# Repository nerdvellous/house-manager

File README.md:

house-manager
=============

Repository du projet "HouseManager"

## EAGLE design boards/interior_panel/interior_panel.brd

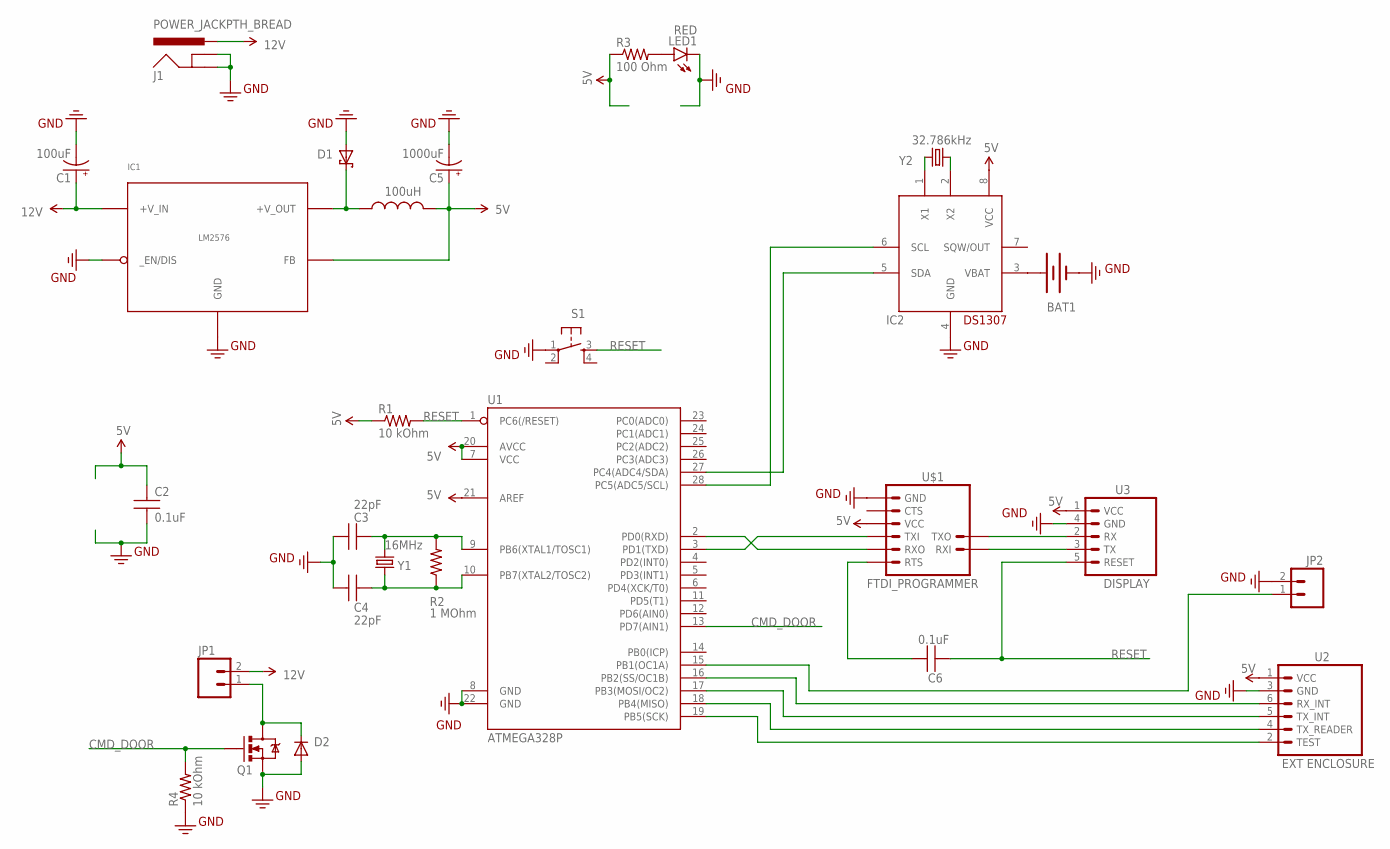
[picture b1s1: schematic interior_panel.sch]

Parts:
BAT1: BATTERY12MMFULLPTH; BATTCON_12MM_FULLPTH
C1: 100uF; CPOL-RADIAL-100UF-25V
C2, C6: 0.1uF; CAP-PTH-SMALL
C3, C4: 22pF; CAP-PTH-SMALL
C5: 1000uF; CPOL-RADIAL-100UF-25V
D1: 1N5822; DO-201AD
D2: 1N4004; DO-41
IC1: LM2576; TO-220-5PIN
IC2: DS1307; DIL08
J1: POWER_JACKPTH_BREAD; POWER_JACK_PTH_BREAD
JP1, JP2: M02PTH; 1X02
L1: 100uH; RLB0912
LED1: RED; LED5MM
Q1: MOSFET-NCHANNELFQP30N06L; TO220V
R1, R4: 10 kOhm; AXIAL-0.3
R2: 1 MOhm; AXIAL-0.3
R3: 100 Ohm; AXIAL-0.3
S1: TAC_SWITCHPTH; TACTILE-PTH
U1: ATMEGA328P; DIL28
U2: EXT ENCLOSURE; 1X06_POL
U3: DISPLAY; 1X05_POL
U$1: FTDI_PROGRAMMER; FTDI_CABLE_JUMPER
Y1: 16MHz; HC49US
Y2: 32.786kHz; TC26V

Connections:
5V: C2.1, C5.1 (+), IC1.P$4 (FB), IC2.8 (VCC), L1.2, R1.P$1 (1), R3.P$1 (1), U1.7 (VCC), U1.20 (AVCC), U1.21 (AREF), U2.1 (VCC), U3.1 (VCC), U$1.VCC
12V: C1.1 (+), IC1.P$1 (+V_IN), J1.PWR, JP1.2
CMD_DOOR: Q1.1 (G), R4.P$2 (2), U1.13 (PD7(AIN1))
GND: BAT1.-, C1.2 (-), C2.2, C3.2, C4.2, C5.2 (-), D1.A, D2.A, IC1.P$3 (GND), IC1.P$5 (_EN/DIS), IC2.4 (GND), J1.GND, J1.GNDBREAK, JP2.2, LED1.K (C), Q1.3 (S), R4.P$1 (1), S1.1, U1.8 (GND), U1.22 (GND), U2.3 (GND), U3.4 (GND), U$1.GND
unnamed: D1.C, IC1.P$2 (+V_OUT), L1.1
unnamed: U1.2 (PD0(RXD)), U$1.TXFTDI (RXO)
unnamed: D2.C, JP1.1, Q1.2 (D)
unnamed: U1.3 (PD1(TXD)), U$1.RXFTDI (TXI)
unnamed: U3.3 (TX), U$1.RXIC (RXI)
unnamed: U3.2 (RX), U$1.TXIC (TXO)
unnamed: C3.1, R2.P$2 (2), U1.9 (PB6(XTAL1/TOSC1)), Y1.2
unnamed: LED1.A, R3.P$2 (2)
unnamed: C4.1, R2.P$1 (1), U1.10 (PB7(XTAL2/TOSC2)), Y1.1
unnamed: C6.2, U$1.RTS
unnamed: IC2.1 (X1), Y2.1
unnamed: IC2.2 (X2), Y2.2
unnamed: BAT1.+1 (+), BAT1.+2 (+), IC2.3 (VBAT)
unnamed: IC2.6 (SCL), U1.28 (PC5(ADC5/SCL))
unnamed: IC2.5 (SDA), U1.27 (PC4(ADC4/SDA))
unnamed: U1.18 (PB4(MISO)), U2.4 (TX_READER)
unnamed: U1.16 (PB2(SS/OC1B)), U2.6 (RX_INT)
unnamed: U1.17 (PB3(MOSI/OC2)), U2.5 (TX_INT)
unnamed: U1.19 (PB5(SCK)), U2.2 (TEST)
unnamed: JP2.1, U1.15 (PB1(OC1A))
RESET: C6.1, R1.P$2 (2), S1.3, U1.1 (PC6(/RESET)), U3.5 (RESET)

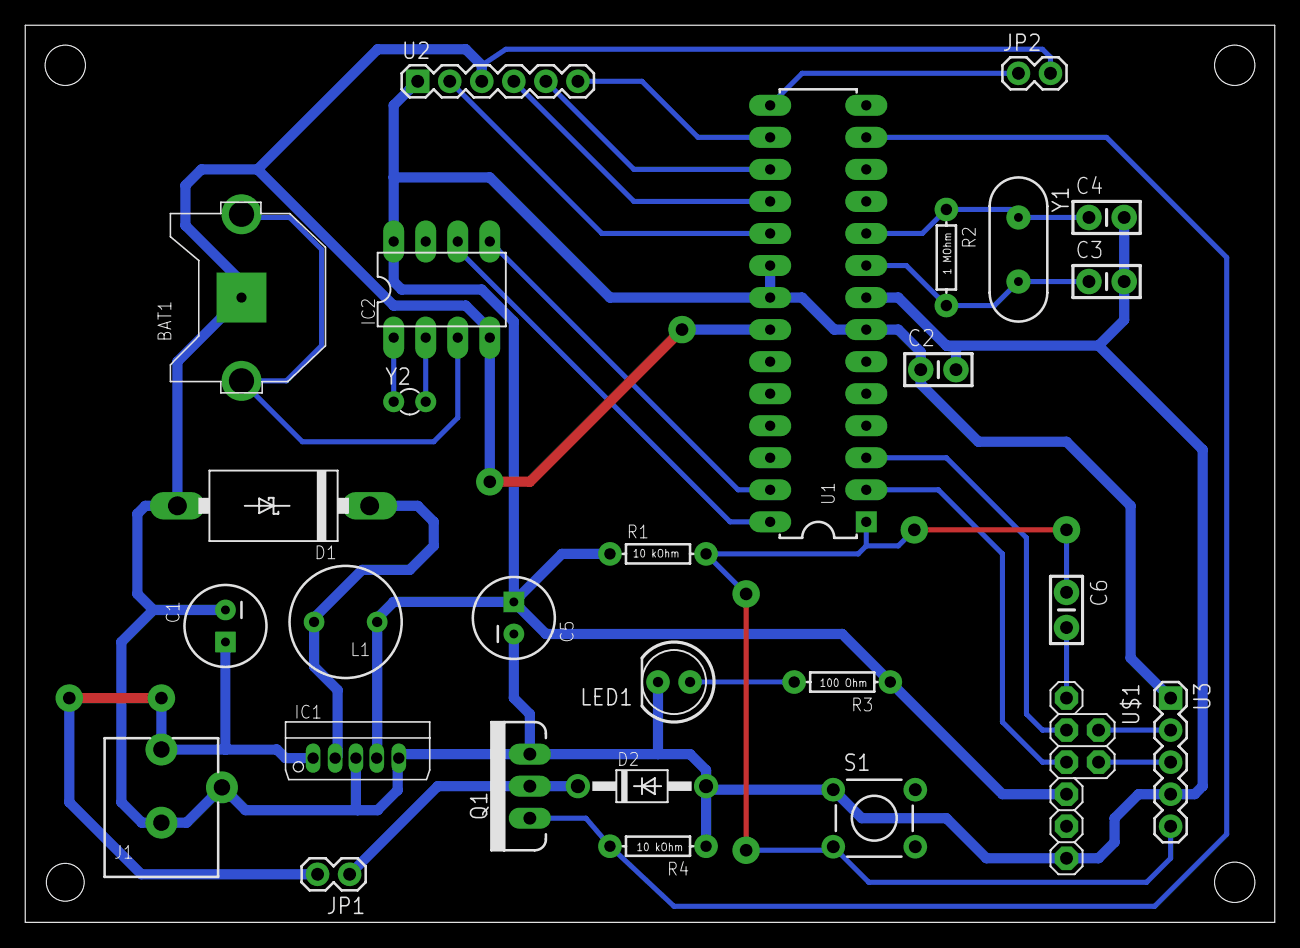
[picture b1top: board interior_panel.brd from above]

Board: 2 copper layers, 99.1 x 71.1 mm, 28 parts (0 on the bottom side), 25 nets.

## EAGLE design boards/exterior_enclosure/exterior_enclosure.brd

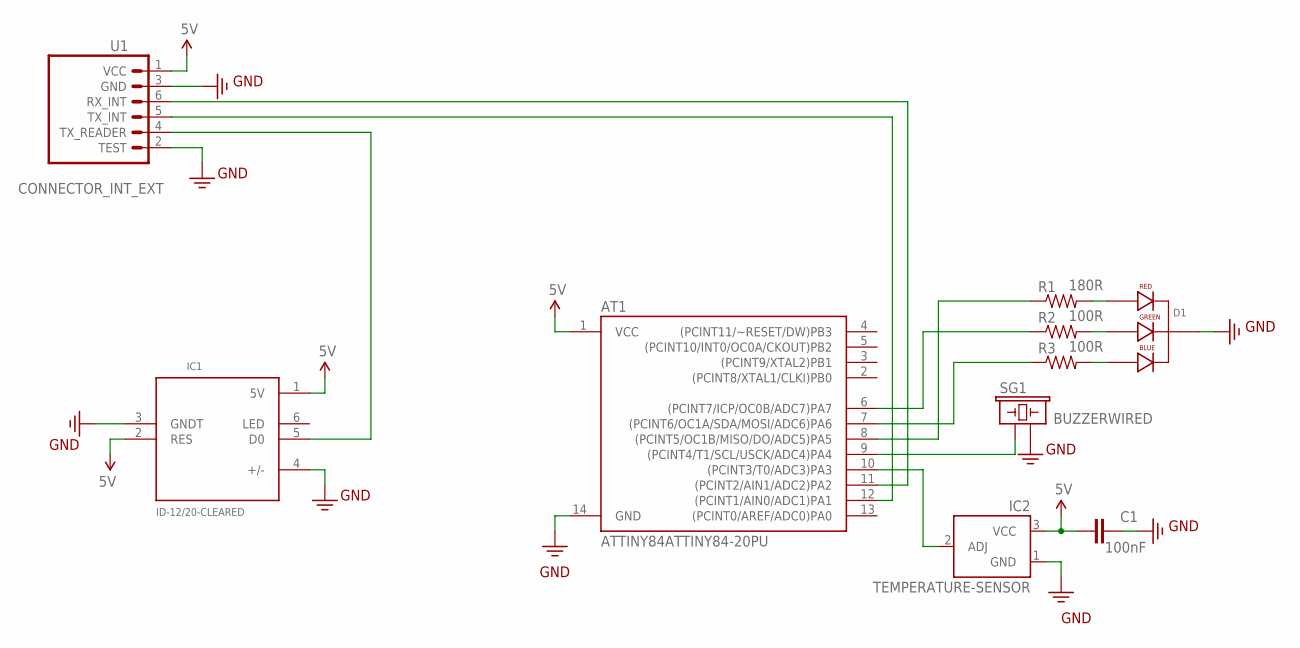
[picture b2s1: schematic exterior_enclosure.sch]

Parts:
AT1: ATTINY84ATTINY84-20PU; DIL14
C1: 100nF; CAP-PTH-SMALL-KIT
D1: LED-RGB-CC-THRUCLEAR; LED-RGB-THRU
IC1: ID-12/20-CLEARED; 1X06_COMMON
IC2: TEMPERATURE-SENSOR; TO-92
R1: 180R; AXIAL-0.1
R2, R3: 100R; AXIAL-0.1
SG1: BUZZERWIRED; 1X02
U1: CONNECTOR_INT_EXT; 1X06_COMMON

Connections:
5V: AT1.1 (VCC), C1.1, IC1.1 (5V), IC1.2 (RES), IC2.3 (VCC), U1.1 (VCC)
GND: AT1.14 (GND), C1.2, D1.2 (CATHODE), IC1.3 (GNDT), IC1.4 (+/-), IC2.1 (GND), SG1.2, U1.2 (TEST), U1.3 (GND)
unnamed: D1.1 (RED_CATHODE), R1.P$2 (2)
unnamed: D1.3 (GREEN_CATHODE), R2.P$2 (2)
unnamed: D1.4 (BLUE_CATHODE), R3.P$2 (2)
unnamed: AT1.10 ((PCINT3/T0/ADC3)PA3), IC2.2 (ADJ)
unnamed: AT1.7 ((PCINT6/OC1A/SDA/MOSI/ADC6)PA6), R3.P$1 (1)
unnamed: AT1.8 ((PCINT5/OC1B/MISO/DO/ADC5)PA5), R1.P$1 (1)
unnamed: AT1.6 ((PCINT7/ICP/OC0B/ADC7)PA7), R2.P$1 (1)
unnamed: AT1.9 ((PCINT4/T1/SCL/USCK/ADC4)PA4), SG1.1
unnamed: AT1.11 ((PCINT2/AIN1/ADC2)PA2), U1.6 (RX_INT)
unnamed: AT1.12 ((PCINT1/AIN0/ADC1)PA1), U1.5 (TX_INT)
unnamed: IC1.5 (D0), U1.4 (TX_READER)

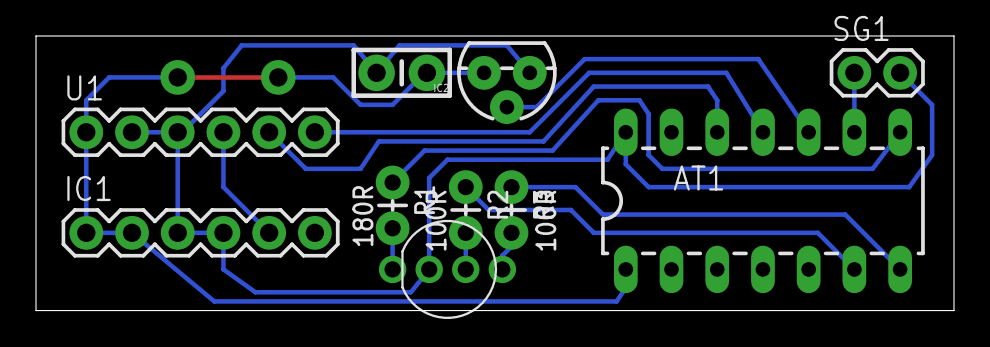
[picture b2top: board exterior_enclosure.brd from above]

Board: 2 copper layers, 51.0 x 15.3 mm, 10 parts (0 on the bottom side), 13 nets.

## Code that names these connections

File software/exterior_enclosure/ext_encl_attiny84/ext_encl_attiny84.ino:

/**
 * Project : house-manager
 * File : ext_encl_attiny84.ino
 * This is the program run by the attiny84 in the exterior enclosure.
 * It receives commands from the control panel and send the exterior temperature
 * if needed.
 *
 * Copyright (C) 2014 nerdvellous
 *
 * This program is free software; you can redistribute it and/or modify
 * it under the terms of the GNU General Public License as published by
 * the Free Software Foundation; either version 2 of the License, or
 * (at your option) any later version.
 *
 * This program is distributed in the hope that it will be useful,
 * but WITHOUT ANY WARRANTY; without even the implied warranty of
 * MERCHANTABILITY or FITNESS FOR A PARTICULAR PURPOSE. See the
 * GNU General Public License for more details.
 *
 * You should have received a copy of the GNU General Public License along
 * with this program; if not, write to the Free Software Foundation, Inc.,
 * 51 Franklin Street, Fifth Floor, Boston, MA 02110-1301 USA.
 */

#include <SoftwareSerial.h>

/*
 * Serial communication with the main board
 */
SoftwareSerial comm(9, 8); // RX, TX

/*
 * pin mapping
 */
#define REDPin 5    // red pin (PWM)
#define GREENPin 3  // green pin (PWM)
#define BLUEPin 4   // blue pin (PWM)
#define BUZZPin 6  // temperature sensor
#define TEMPPin A3  // temperature sensor

/*
 * color mapping
 */
unsigned char color_mapping[6][3] = {
  {0,0,0}, // 0 : none
  {255,0,0}, // 1 : red
  {0,255,0}, // 2 : green
  {0,0,255}, // 3 : blue
  {255,50,0}, // 4 : yellow
  {255,255,150}, // 5 : white
};

/*
 * Get the tempetrature from the sensor (in celsius).
 * If the temperature is negative, the function returns
 * the additive inverse of the value plus 100.
 * For instance -7 will become 107.
 */
char get_temp() {
  int sensorValue = analogRead(TEMPPin);
  float voltage = sensorValue * 5;
  voltage /= 1024.0;
  float temperatureC = (voltage - 0.5) * 100; 
  
  if (temperatureC < 0) {
    return temperatureC*-1+100;
  } else {
    return temperatureC;
  }
}

/*
 * Manage the led
 */
void led(unsigned char rgb[]) {
  analogWrite(REDPin, rgb[0]);
  analogWrite(GREENPin, rgb[1]);
  analogWrite(BLUEPin, rgb[2]);
}

/*
 * Buzz
 */
void buzz() {
  digitalWrite(BUZZPin, HIGH);
  delay(400);
  digitalWrite(BUZZPin, LOW); 
}

// SETUP
void setup() {
  comm.begin(9600);
  pinMode(REDPin, OUTPUT);
  pinMode(GREENPin, OUTPUT);
  pinMode(BLUEPin, OUTPUT);
  pinMode(BUZZPin, OUTPUT);
  analogReference(DEFAULT);
}

// LOOP
/* Command list :
 * r : led to red
 * g : led to green
 * b : led to blue
 * y : led to yellow
 * w : led to white
 * n : led faded
 */
void loop() {
  if (comm.available()) {
    char command = comm.read();
    if (command == 'r') {
      led(color_mapping[1]);
    } else if (command == 'g') {
      led(color_mapping[2]);
    } else if (command == 'b') {
      led(color_mapping[3]);
    } else if (command == 'y') {
      led(color_mapping[4]);
    } else if (command == 'w') {
      led(color_mapping[5]);
    } else if (command == 'n') {
      led(color_mapping[0]);
    } else if (command == 'z') {
      buzz();
    } else if (command == 't') {
      comm.write(get_temp()); 
    }
  }
}

// ATMEL ATTINY84 / ARDUINO
//
//                           +-\/-+
//                     VCC  1|    |14  GND
//             (D  0)  PB0  2|    |13  AREF (D 10)
//             (D  1)  PB1  3|    |12  PA1  (D  9) 
//                     PB3  4|    |11  PA2  (D  8) 
//  PWM  INT0  (D  2)  PB2  5|    |10  PA3  (D  7) 
//  PWM        (D  3)  PA7  6|    |9   PA4  (D  6) 
//  PWM        (D  4)  PA6  7|    |8   PA5  (D  5)        PWM
//                           +----+

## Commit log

2014-07-21 Premier commit
2014-07-29 new file tree
2014-07-30 Interior panel commit
2014-07-30 Interior open command added
2014-07-30 DRC check
2014-07-30 Initial software commit
2014-08-01 PCB Update
2014-08-06 100 Ohm resistor for the power led
2014-08-06 Bigger power track (5V, 12V, and GND)
2014-08-06 Initial commit
    This is the file to patch to upload the program into the attiny84
2014-08-06 Fix the temperature bug
2014-08-06 Communication with the exterior enclosure
2014-08-06 Initial commit
    This is the arduino library used to upload codes into the attiny84
